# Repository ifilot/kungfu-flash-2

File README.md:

# Kung Fu Flash 2 - Adapted version

Cartridge for the Commodore 64 that packs a punch.

> [!IMPORTANT]  
> This repository is a fork of [Kung Fu Flash 2](https://github.com/KimJorgensen/KungFuFlash2).
> A number of changes have been made to the original design, mainly focusing
> on using so-called "BASIC" parts to reduce upon the cost of using the JLCPCB
> assembly service.
>
> In the folder [hardware/production](hardware/production) one can find the
> BOM and CPL files for using the JLCPCB assembly service.
>
> 

**The text below has been copied verbatim from the original repository**

Kung Fu Flash 2 is the big brother of [Kung Fu Flash](https://github.com/KimJorgensen/KungFuFlash). It has a faster microcontroller with more memory and I/O pins, allowing for additional functionality.

**Currently, this project is considered experimental** and provides the same features as Kung Fu Flash, with these notable exceptions:

* CRT files are loaded into RAM, not flash, making large CRT files startup faster. However, changes to EasyFlash cartridges are lost if power is turned off, unless saved via the menu first
* The cartridge detects if the C64/C128 is reset. This allows the use of an additional reset button on the C64 or the built-in reset button on the C128
* REU emulation has been added

Kung Fu Flash 2 can emulate different cartridge types, load PRG files and use D64 disk images.
Just place your desired CRT, PRG or D64 files on a FAT formatted microSD card and use the built-in launcher to execute them.

## Hardware

There are three buttons on the cartridge; a reset button, a menu button for starting the launcher, and a special button that is used by the freezer cartridges.

The form factor is similar to Kung Fu Flash and it should be possible to use the same cartridge cases.
It could be the Stumpy Cartridge Case from TFW8b or the 3D printed cartridge case designed by bigby, [see here](https://www.thingiverse.com/thing:4153414).

The gerber files and BOM can be found [here](https://github.com/KimJorgensen/KungFuFlash2/releases/tag/v2.00).

## Supported Cartridges

The following cartridge types are currently supported:

* Generic cartridge (8k, 16k, Ultimax)
* Action Replay v4.x/v5/v6
* KCS Power Cartridge
* Final Cartridge III(+)
* Simons' BASIC
* Fun Play, Power Play
* Super Games
* Ocean type 1
* Epyx Fastload
* C64 Game System, System 3
* WarpSpeed
* Dinamic
* Zaxxon, Super Zaxxon
* Magic Desk, Domark, HES Australia
* Super Snapshot v5
* Comal-80
* Ross
* EasyFlash
* Prophet64
* Freeze Frame
* Freeze Machine
* MACH 5
* Pagefox
* RGCD, Hucky
* Drean
* C128 Generic cartridge (external function ROM)
* WarpSpeed 128

## Supported File Types

The following file types are currently supported:

* Cartridge (CRT)
* C64/C128 generic cartridge (ROM, BIN)
* Disk image (D64, D71, D81)
* Tape image (T64)
* Program (PRG, P00)
* Firmware update (UPD)
* Text document (TXT, NFO, 1ST)

## REU Emulation

Kung Fu Flash 2 can emulate a 1 Mb REU (RAM Expansion Unit) simultaneously with disk drive emulation.
The REU is enabled in the settings menu (F5) and active when:

* A program is executed using the default option (RETURN)
* A disk image or directory is mounted using "Mount" in the file options menu (SHIFT+RETURN)
* BASIC is started via F6 (C128) or F7 (C64) in the launcher

The REU will not be active when emulating cartridges (CRT files)

## USB Port

The USB port allows programs or disk images to be transferred from/to a PC using the EasyFlash 3 USB protocol.
The USB port is active when:

* The Kung Fu Flash 2 launcher is running
* A program is started using "Load" in the file options menu (SHIFT+RETURN)
* BASIC is started via F7 in the launcher **and** REU emulation is disabled in the settings menu (F5)

Kung Fu Flash 2 shows up as a standard serial port when connected to a PC not requiring any custom drivers to be installed.
This means, however, that the EasyFlash 3 program on the PC side must be modified to support Kung Fu Flash.

The repository of the original Kung Fu Flash contains a modified version of [EasyFlash 3 USB Utilities](https://github.com/KimJorgensen/KungFuFlash/tree/master/3rd_party/ef3utils)
and [EasyFlash 3 BBS](https://github.com/KimJorgensen/KungFuFlash/tree/master/3rd_party/ef3bbs) which will also work with the Kung Fu Flash 2.

## Firmware Update

Just place the KungFuFlash_v2.xx.upd file on the SD card and select the file in the launcher to initiate the firmware update.
The newest firmware can be found [here](https://github.com/KimJorgensen/KungFuFlash2/releases/).

For initial firmware installation, [see here](firmware/README.md).

## Limitations

Kung Fu Flash 2 is a so called Software Defined Cartridge where a fast microcontroller emulates cartridge hardware in software.
This makes it extremely flexible, allowing different cartridge types to be supported at a relative low cost.

However, it can be challenging to get the C64 bus timing correct in software and in some places the timing is very close to the limit.
Even though Kung Fu Flash 2 has been tested on different models of the Commodore 64, there is a chance that it doesn't work correctly on your specific model, or requires [phi2 offset adjustment](firmware/README.md#diagnostic).
Use it at your own risk!

Kung Fu Flash 2 will work with the PAL and NTSC version of the Commodore 64 or Commodore 128.

Disk drive emulation is using kernal vectors and will not work with fast loaders or software that uses direct hardware access which a lot of games does.
Currently REL files are not supported and only a subset of the Commodore DOS commands are supported.

## Thanks

Kung Fu Flash 2 was based on or uses other open source projects:

* [Kung Fu Flash](https://github.com/KimJorgensen/KungFuFlash)
* [EasyFlash 3](https://bitbucket.org/skoe/easyflash) by Thomas Giesel
* [Draco Browser](https://csdb.dk/release/?id=89910) by Sascha Bader
* [fatfs-stm32](https://github.com/colosimo/fatfs-stm32) by Aurelio Colosimo
* [FatFs](http://elm-chan.org/fsw/ff/00index_e.html) by ChaN
* [libusb_stm32](https://github.com/dmitrystu/libusb_stm32) by Dmitry Filimonchuk
* [OpenC64Cart](https://github.com/SukkoPera/OpenC64Cart) by Giorgioggì
* [Disk2easyflash](https://csdb.dk/release/?id=150323) by ALeX Kazik

and a few others. Please check the individual files for their license.

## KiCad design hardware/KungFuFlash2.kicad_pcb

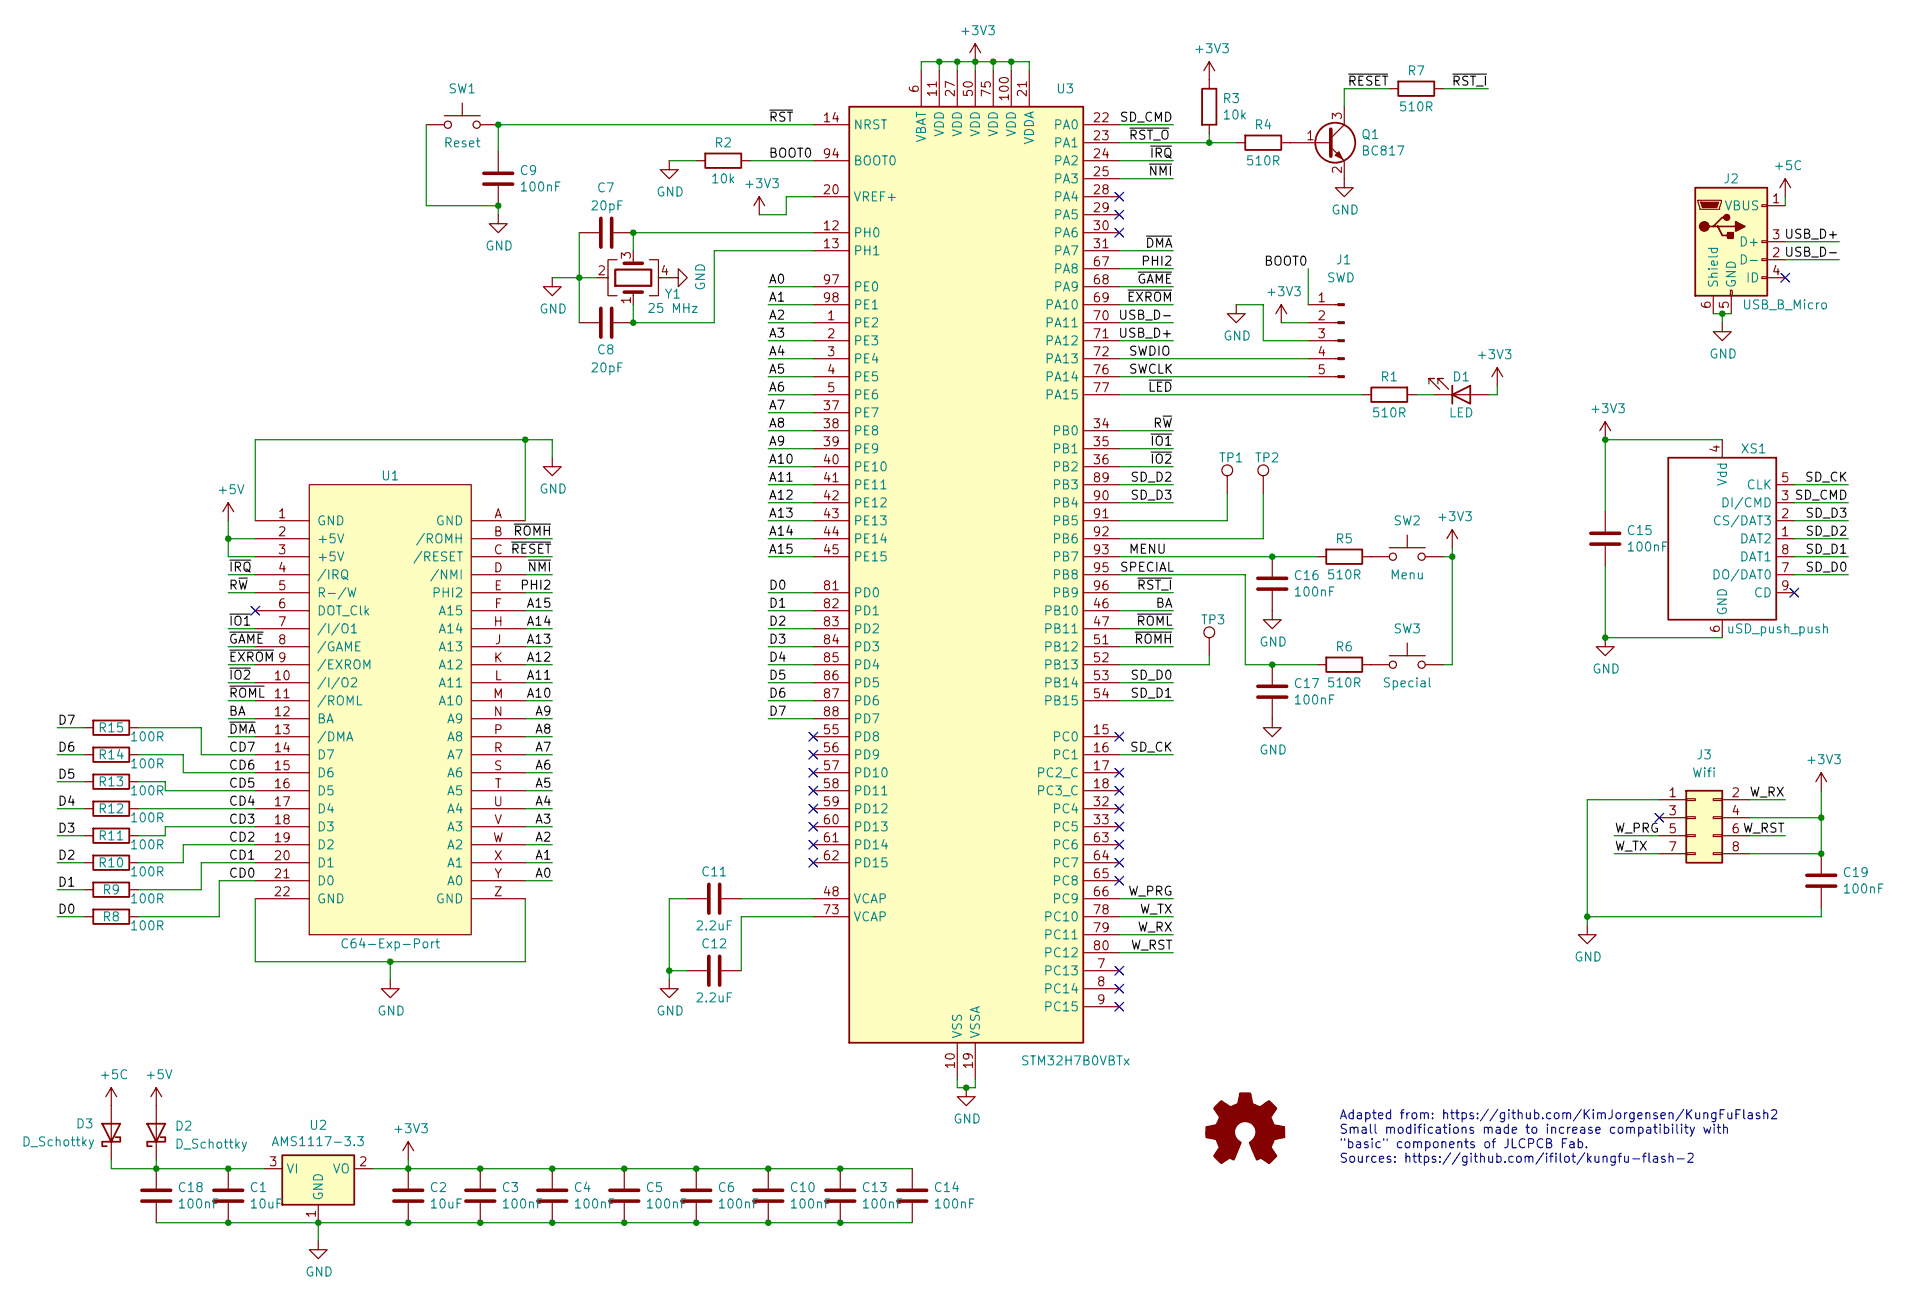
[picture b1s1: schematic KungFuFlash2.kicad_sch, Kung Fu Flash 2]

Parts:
C1, C2: 10uF; C_0805_2012Metric_Pad1.18x1.45mm_HandSolder; LCSC Part # C15850
C3, C4, C5, C6, C9, C10, C13, C14, C15, C16, C17, C18, C19: 100nF; C_0603_1608Metric_Pad1.08x0.95mm_HandSolder; LCSC Part # C14663
C7, C8: 20pF; C_0603_1608Metric_Pad1.08x0.95mm_HandSolder; LCSC Part # C1648
C11, C12: 2.2uF; C_0805_2012Metric_Pad1.18x1.45mm_HandSolder; LCSC Part # C377773
D1: LED; LED_0805_2012Metric_Pad1.15x1.40mm_HandSolder; LCSC Part # C2297
D2, D3: D_Schottky; D_SMA_Handsoldering; LCSC Part # C14996
J1: SWD; PinHeader_1x05_P2.54mm_Vertical
J2: USB_B_Micro; Conn_USBmini_reichelt; LCSC Part # C46391
J3: Wifi; PinSocket_2x04_P2.54mm_Vertical
Q1: BC817; SOT-23; LCSC Part # C466643
R1, R4, R5, R6, R7: 510R; R_0805_2012Metric_Pad1.20x1.40mm_HandSolder; LCSC Part # C17734
R2, R3: 10k; R_0805_2012Metric_Pad1.20x1.40mm_HandSolder; LCSC Part # C17414
R8, R9, R10, R11, R12, R13, R14, R15: 100R; R_0805_2012Metric_Pad1.20x1.40mm_HandSolder; LCSC Part # C17408
SW1: Reset; SW_PUSH_6mm_H8mm; LCSC Part # C134186
SW2: Menu; SW_PUSH_6mm_H8mm; LCSC Part # C134186
SW3: Special; SW_PUSH_6mm_H8mm; LCSC Part # C134186
TP1, TP2, TP3: TestPoint_Pad_1.0x1.0mm
U1: C64-Exp-Port; C64-Cart
U2: AMS1117-3.3; SOT-223-3_TabPin2; LCSC Part # C6186
U3: STM32H7B0VBTx; LQFP-100_14x14mm_P0.5mm; LCSC Part # C730227
XS1: uSD_push_push; Conn_uSDcard; LCSC Part # C91145
Y1: 25 MHz; Crystal_SMD_3225-4Pin_3.2x2.5mm; LCSC Part # C9006

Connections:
+3V3: C2.1, C3.1, C4.1, C5.1, C6.1, C10.1, C13.1, C14.1, C15.1, C19.1, D1.2 (A), J1.2, J3.4, J3.8, R3.1, SW2.1, SW3.1, U2.2 (VO), U3.6 (VBAT), U3.11 (VDD), U3.20 (VREF+), U3.21 (VDDA), U3.27 (VDD), U3.50 (VDD), U3.75 (VDD), U3.100 (VDD), XS1.4 (Vdd)
+5C: D3.2 (A), J2.1 (VBUS)
+5V: D2.2 (A), U1.2 (+5V), U1.3 (+5V)
/A0: U1.Y (A0), U3.97 (PE0)
/A1: U1.X (A1), U3.98 (PE1)
/A2: U1.W (A2), U3.1 (PE2)
/A3: U1.V (A3), U3.2 (PE3)
/A4: U1.U (A4), U3.3 (PE4)
/A5: U1.T (A5), U3.4 (PE5)
/A6: U1.S (A6), U3.5 (PE6)
/A7: U1.R (A7), U3.37 (PE7)
/A8: U1.P (A8), U3.38 (PE8)
/A9: U1.N (A9), U3.39 (PE9)
/A10: U1.M (A10), U3.40 (PE10)
/A11: U1.L (A11), U3.41 (PE11)
/A12: U1.K (A12), U3.42 (PE12)
/A13: U1.J (A13), U3.43 (PE13)
/A14: U1.H (A14), U3.44 (PE14)
/A15: U1.F (A15), U3.45 (PE15)
/BA: U1.12 (BA), U3.46 (PB10)
/BOOT0: J1.1, R2.1, U3.94 (BOOT0)
/CD0: R8.1, U1.21 (D0)
/CD1: R9.1, U1.20 (D1)
/CD2: R10.1, U1.19 (D2)
/CD3: R11.1, U1.18 (D3)
/CD4: R12.1, U1.17 (D4)
/CD5: R13.1, U1.16 (D5)
/CD6: R14.1, U1.15 (D6)
/CD7: R15.1, U1.14 (D7)
/D0: R8.2, U3.81 (PD0)
/D1: R9.2, U3.82 (PD1)
/D2: R10.2, U3.83 (PD2)
/D3: R11.2, U3.84 (PD3)
/D4: R12.2, U3.85 (PD4)
/D5: R13.2, U3.86 (PD5)
/D6: R14.2, U3.87 (PD6)
/D7: R15.2, U3.88 (PD7)
/MENU: C16.1, R5.2, U3.93 (PB7)
/PHI2: U1.E (PHI2), U3.67 (PA8)
/R~W: U1.5 (R-/W), U3.34 (PB0)
/SD_CK: U3.16 (PC1), XS1.5 (CLK)
/SD_CMD: U3.22 (PA0), XS1.3 (DI/CMD)
/SD_D0: U3.53 (PB14), XS1.7 (DO/DAT0)
/SD_D1: U3.54 (PB15), XS1.8 (DAT1)
/SD_D2: U3.89 (PB3), XS1.1 (DAT2)
/SD_D3: U3.90 (PB4), XS1.2 (CS/DAT3)
/SPECIAL: C17.1, R6.2, U3.95 (PB8)
/SWCLK: J1.5, U3.76 (PA14)
/SWDIO: J1.4, U3.72 (PA13)
/USB_D+: J2.3 (D+), U3.71 (PA12)
/USB_D-: J2.2 (D-), U3.70 (PA11)
/W_PRG: J3.5, U3.66 (PC9)
/W_RST: J3.6, U3.80 (PC12)
/W_RX: J3.2, U3.79 (PC11)
/W_TX: J3.7, U3.78 (PC10)
/~DMA: U1.13 (/DMA), U3.31 (PA7)
/~EXROM: U1.9 (/EXROM), U3.69 (PA10)
/~GAME: U1.8 (/GAME), U3.68 (PA9)
/~IO1: U1.7 (/I/O1), U3.35 (PB1)
/~IO2: U1.10 (/I/O2), U3.36 (PB2)
/~IRQ: U1.4 (/IRQ), U3.24 (PA2)
/~LED: R1.1, U3.77 (PA15)
/~NMI: U1.D (/NMI), U3.25 (PA3)
/~RESET: Q1.3 (C), R7.2, U1.C (/RESET)
/~ROMH: U1.B (/ROMH), U3.51 (PB12)
/~ROML: U1.11 (/ROML), U3.47 (PB11)
/~RST_I: R7.1, U3.96 (PB9)
/~RST_O: R3.2, R4.2, U3.23 (PA1)
/~RST: C9.1, SW1.2, U3.14 (NRST)
GND: C1.2, C2.2, C3.2, C4.2, C5.2, C6.2, C7.1, C8.1, C9.2, C10.2, C11.1, C12.2, C13.2, C14.2, C15.2, C16.2, C17.2, C18.2, C19.2, J1.3, J2.5 (GND), J2.6 (Shield), J3.1, Q1.2 (E), R2.2, SW1.1, U1.1 (GND), U1.22 (GND), U1.A (GND), U1.Z (GND), U2.1 (GND), U3.10 (VSS), U3.19 (VSSA), U3.26 (VSS), U3.49 (VSS), U3.74 (VSS), U3.99 (VSS), XS1.6 (GND), Y1.2, Y1.4
unnamed: C11.2, U3.48 (VCAP)
unnamed: C12.1, U3.73 (VCAP)
unnamed: D1.1 (K), R1.2
unnamed: C1.1, C18.1, D2.1 (K), D3.1 (K), U2.3 (VI)
unnamed: Q1.1 (B), R4.1
unnamed: R5.1, SW2.2
unnamed: R6.1, SW3.2
unnamed: TP1.1, U3.91 (PB5)
unnamed: TP2.1, U3.92 (PB6)
unnamed: TP3.1, U3.52 (PB13)
unnamed: C7.2, U3.12 (PH0), Y1.3
unnamed: C8.2, U3.13 (PH1), Y1.1

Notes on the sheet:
Adapted from: https://github.com/KimJorgensen/KungFuFlash2 Small modifications made to increase compatibility with "basic" components of JLCPCB Fab. Sources: https://github.com/ifilot/kungfu-flash-2

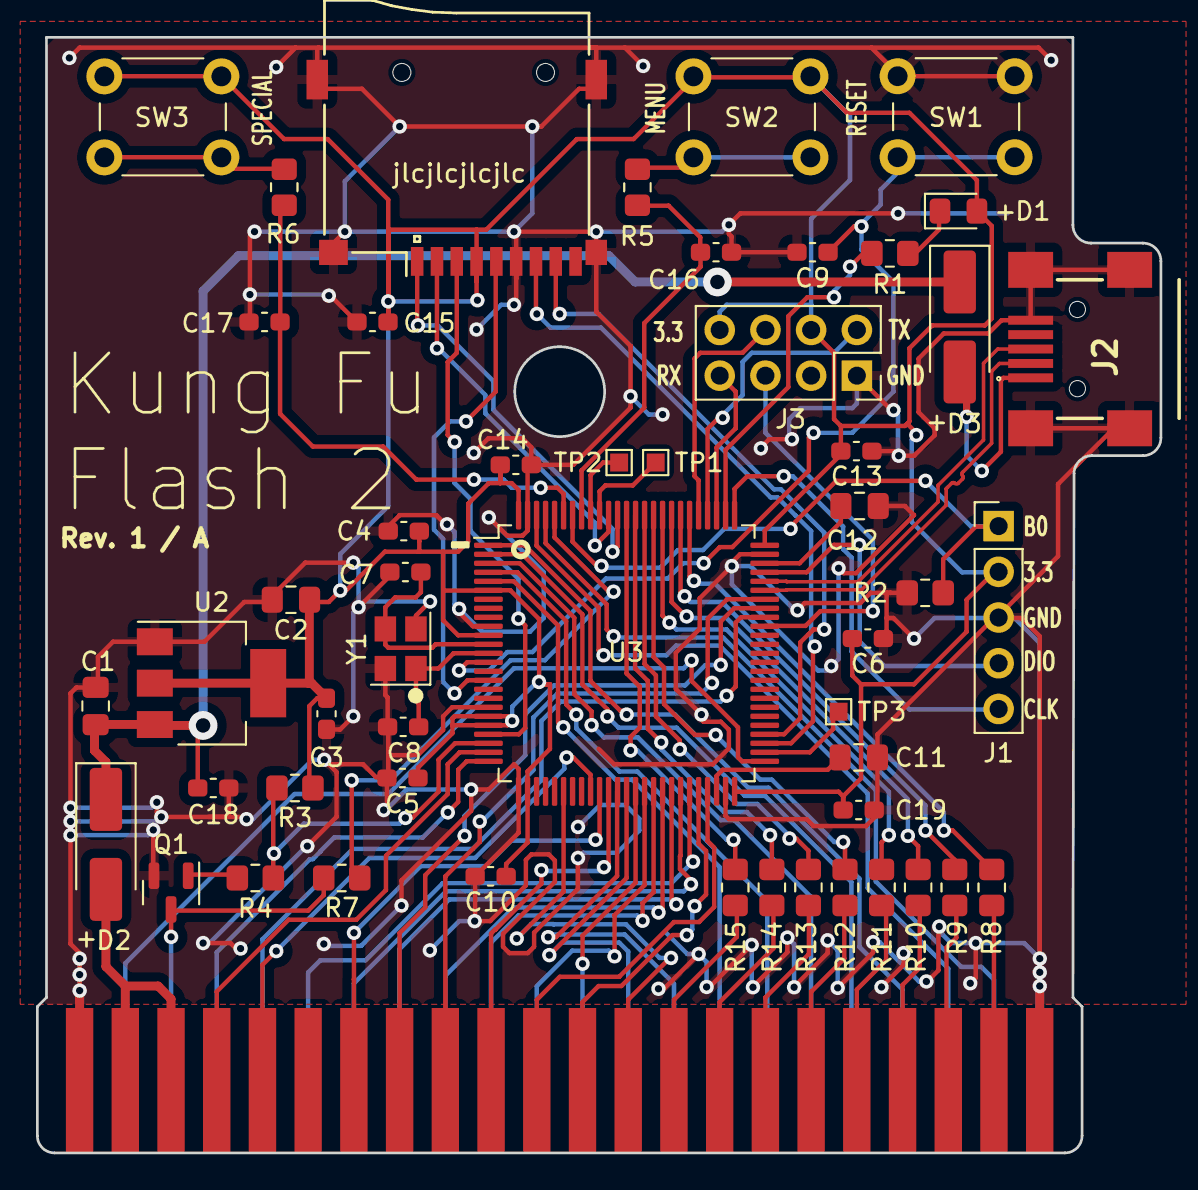
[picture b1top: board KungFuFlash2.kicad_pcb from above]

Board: 2 copper layers, 62.4 x 62.0 mm, 52 parts (0 on the bottom side), 82 nets.

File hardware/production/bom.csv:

Designator,Footprint,Quantity,Value,LCSC Part #
"C1, C2",0805,2,10uF,C15850
"C10, C13, C14, C15, C16, C17, C18, C19, C3, C4, C5, C6, C9",0603,13,100nF,C14663
"C11, C12",0805,2,2.2uF,C377773
"C7, C8",0603,2,20pF,C1648
D1,0805,1,LED,C2297
"D2, D3",D_SMA_Handsoldering,2,D_Schottky,C14996
J1,PinHeader_1x05_P2.54mm_Vertical,1,SWD,
J2,Conn_USBmini_reichelt,1,USB_B_Micro,C46391
J3,PinSocket_2x04_P2.54mm_Vertical,1,Wifi,
Q1,SOT-23,1,BC817,C466643
"R1, R4, R5, R6, R7",0805,5,510R,C17734
"R10, R11, R12, R13, R14, R15, R8, R9",0805,8,100R,C17408
"R2, R3",0805,2,10k,C17414
SW1,SW_PUSH_6mm_H8mm,1,Reset,C134186
SW2,SW_PUSH_6mm_H8mm,1,Menu,C134186
SW3,SW_PUSH_6mm_H8mm,1,Special,C134186
"TP1, TP2, TP3",TestPoint_Pad_1.0x1.0mm,3,~,
U1,C64-Cart,1,C64-Exp-Port,
U2,SOT-223-3_TabPin2,1,AMS1117-3.3,C6186
U3,LQFP-100_14x14mm_P0.5mm,1,STM32H7B0VBTx,C730227
XS1,Conn_uSDcard,1,uSD_push_push,C91145
Y1,Crystal_SMD_3225-4Pin_3.2x2.5mm,1,25 MHz,C9006

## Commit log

2025-03-01 Adapting board for JLCPCB ordering
2025-03-01 Refining design and updating README.md
2025-03-01 Filling out all components
2025-03-01 Fixing wrong component
2025-03-01 Updating image
2025-04-04 Adding enclosure
2025-04-17 Adding flash procedure
